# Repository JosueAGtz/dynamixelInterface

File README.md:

# Dynamixel Interface
The Dynamixel Interface is a board that allows easy communication with an MCU or Processor with a simple UART module, the board integrates a voltage level converter and a Tri-state buffer to accomplish good communication between a Dynamixel servomotor and almost any microcontroller in the market. The board is breadboard-friendly and development-ready as the connection pins are 0.1" standard pitch and the castellated holes for SMD mounting.

Get the assembled interface on my Tindie Store:  https://www.tindie.com/products/17747/

## Dynamixel Interface Wiring 

## Dynamixel Interface Features and Pinout

## Dynamixel Interface Dimensions

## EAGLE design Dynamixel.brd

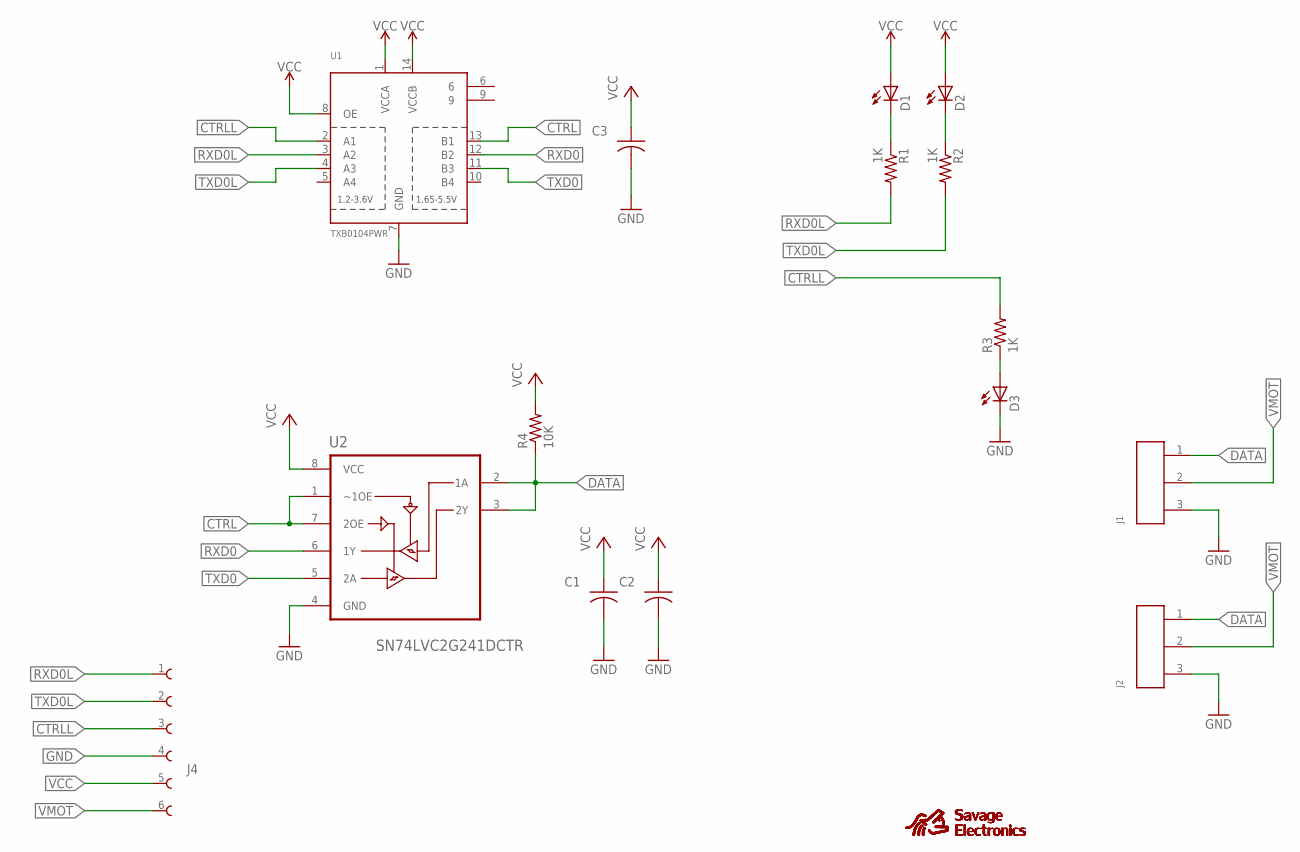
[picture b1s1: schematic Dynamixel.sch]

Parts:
C1, C2, C3: 1uF; C0805
D1, D2, D3: LEDCHIP-LED0805; CHIP-LED0805
J1: 62000311722
J2: 64600311622
J4: 61300611121
R1, R2, R3: 1K; R0805
R4: 10K; R0805
U1: TXB0104PWR; TSSOP14
U2: SN74LVC2G241DCTR; SOP65P400X130-8N
U$2: SE_SMALL_SILK
U$3: SE_SMALL_FSILK; SE_SMALL_FACESILK

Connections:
CTRL: U1.13 (B1), U2.1 (~1OE), U2.7 (2OE)
CTRLL: J4.3, R3.2, U1.2 (A1)
DATA: J1.1, J2.1, R4.1, U2.2 (1A), U2.3 (2Y)
GND: C1.2, C2.2, C3.2, D3.C, J1.3, J2.3, J4.4, U1.7 (GND), U2.4 (GND)
unnamed: D1.C, R1.1
unnamed: D2.C, R2.1
unnamed: D3.A, R3.1
RXD0: U1.12 (B2), U2.6 (1Y)
RXD0L: J4.1, R1.2, U1.3 (A2)
TXD0: U1.11 (B3), U2.5 (2A)
TXD0L: J4.2, R2.2, U1.4 (A3)
VCC: C1.1, C2.1, C3.1, D1.A, D2.A, J4.5, R4.2, U1.1 (VCCA), U1.8 (OE), U1.14 (VCCB), U2.8 (VCC)
VMOT: J1.2, J2.2, J4.6

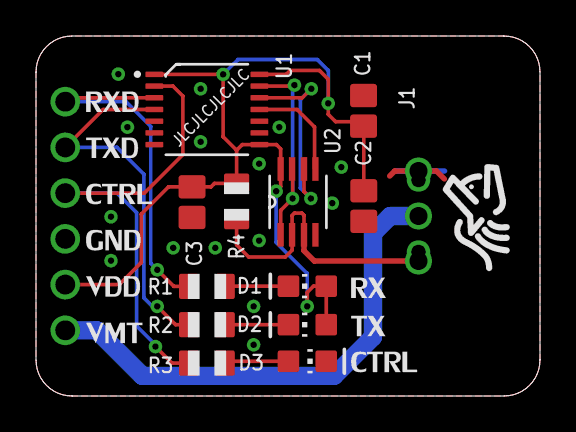
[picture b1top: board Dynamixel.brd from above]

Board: 2 copper layers, 28.0 x 20.0 mm, 17 parts (1 on the bottom side), 13 nets.

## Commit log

2023-10-13 Library Update and examples
2025-01-15 BOM update

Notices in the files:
parts and their libraries:
Wire-to-Board: Copyright: Würth Elektronik
SparkFun-PowerSymbols: Licensing: Creative Commons ShareAlike 4.0 International - https://creativecommons.org/licenses/by-sa/4.0
